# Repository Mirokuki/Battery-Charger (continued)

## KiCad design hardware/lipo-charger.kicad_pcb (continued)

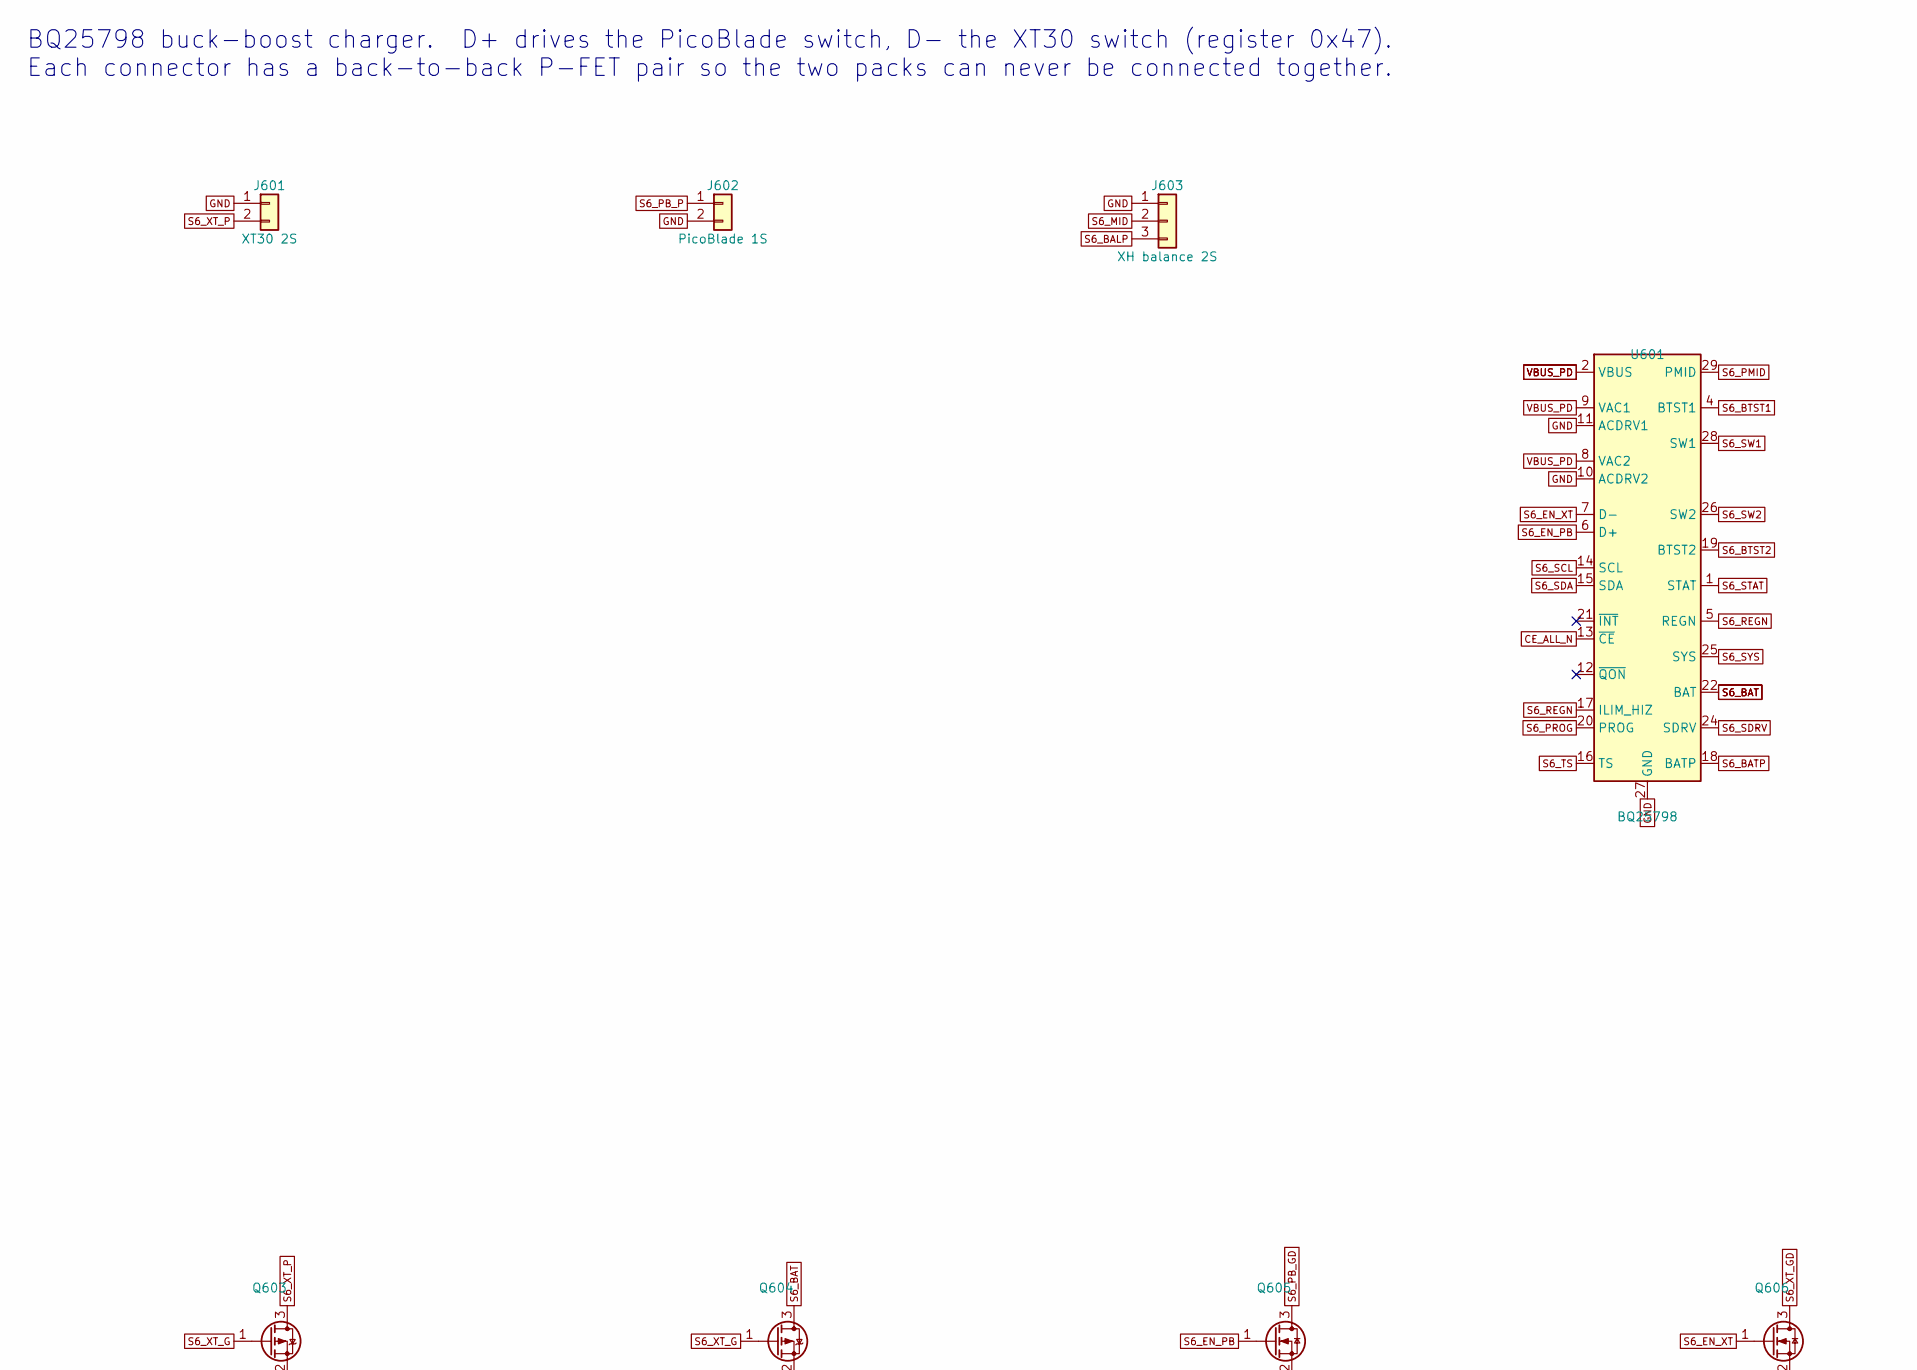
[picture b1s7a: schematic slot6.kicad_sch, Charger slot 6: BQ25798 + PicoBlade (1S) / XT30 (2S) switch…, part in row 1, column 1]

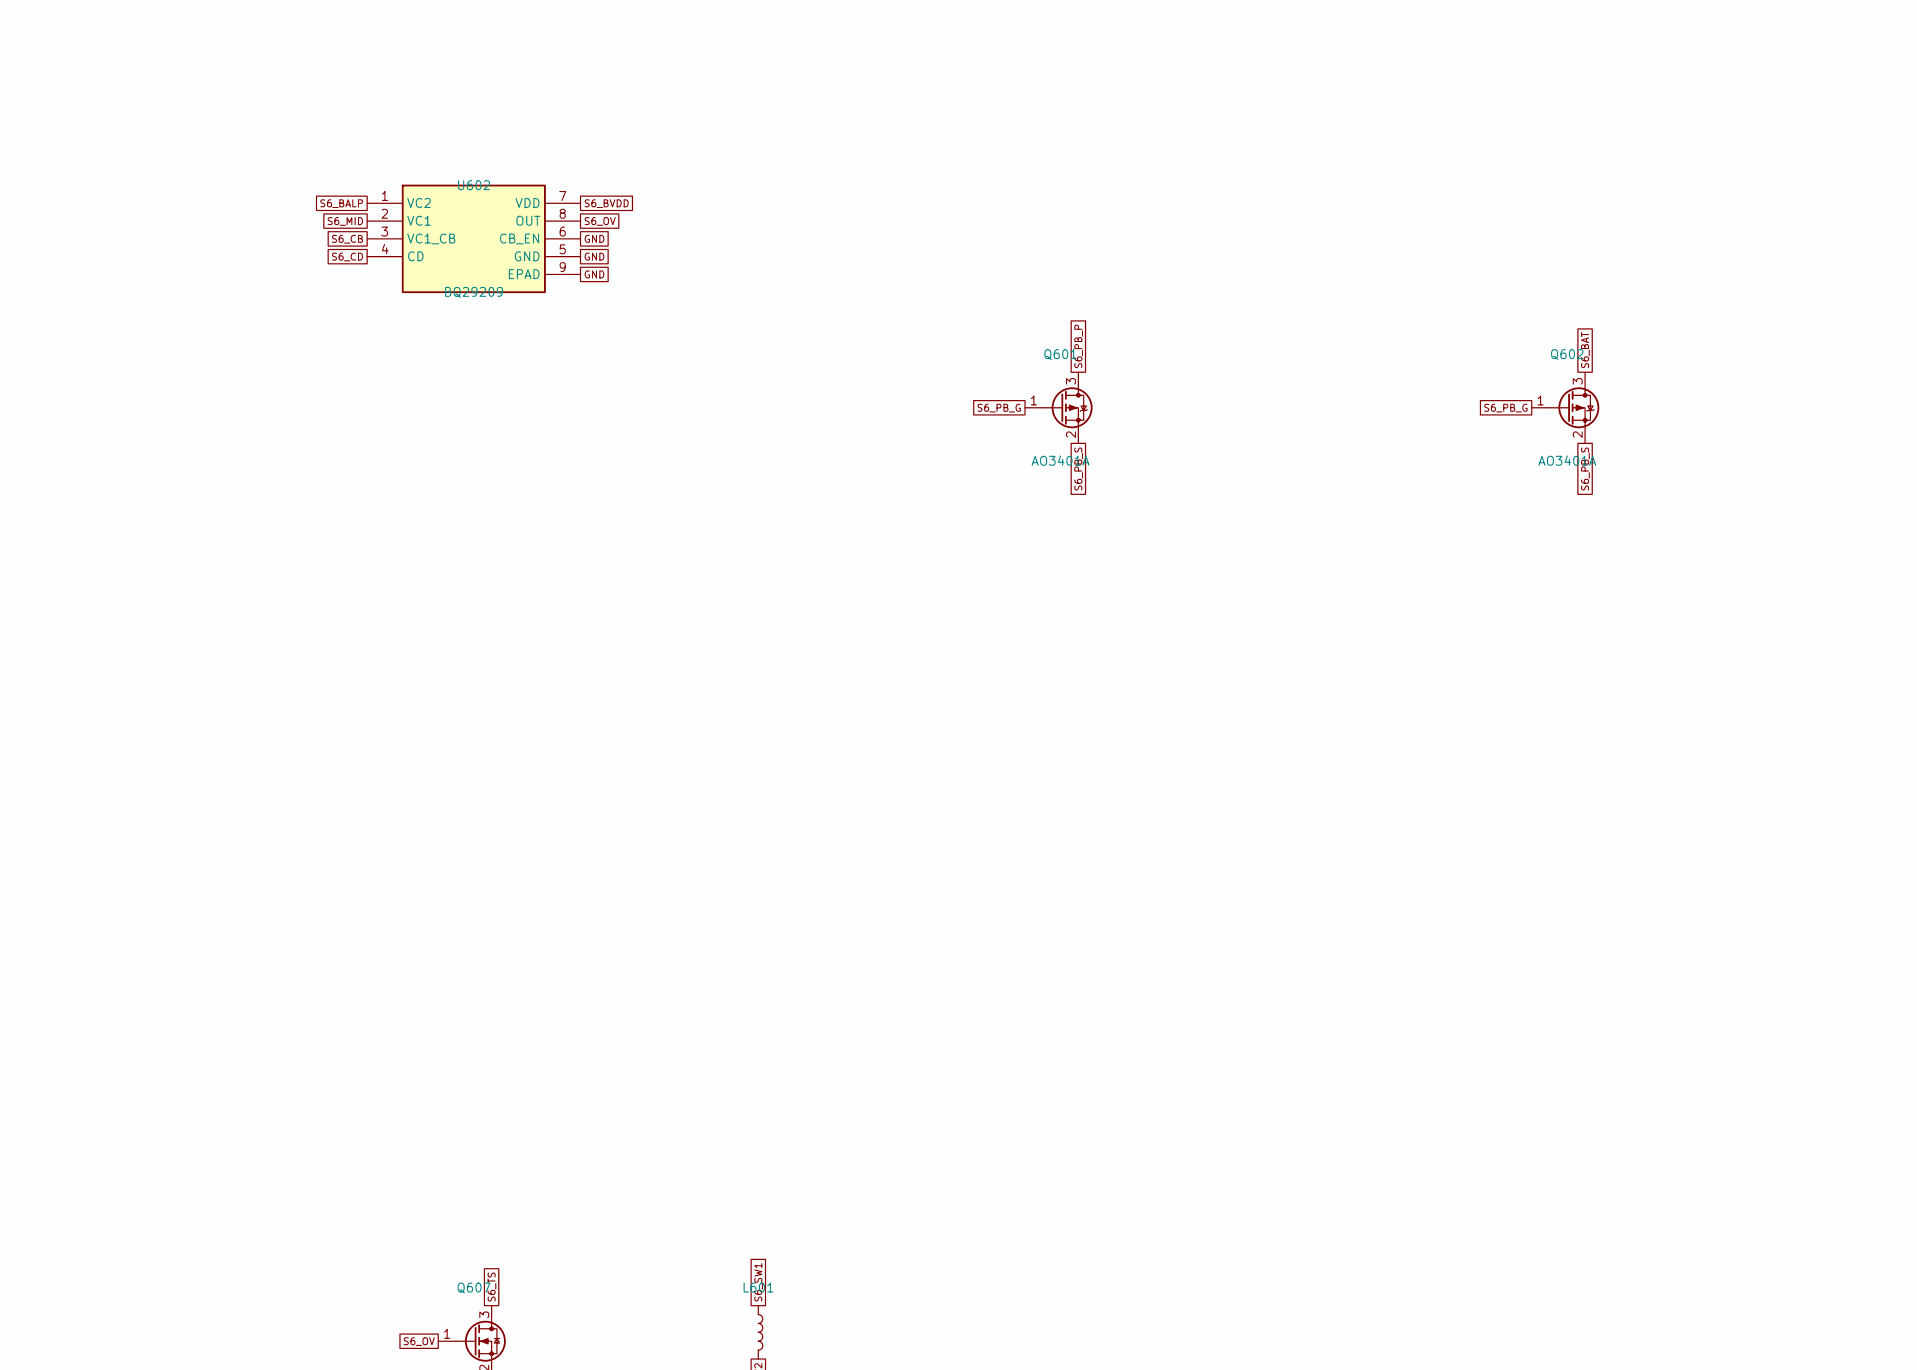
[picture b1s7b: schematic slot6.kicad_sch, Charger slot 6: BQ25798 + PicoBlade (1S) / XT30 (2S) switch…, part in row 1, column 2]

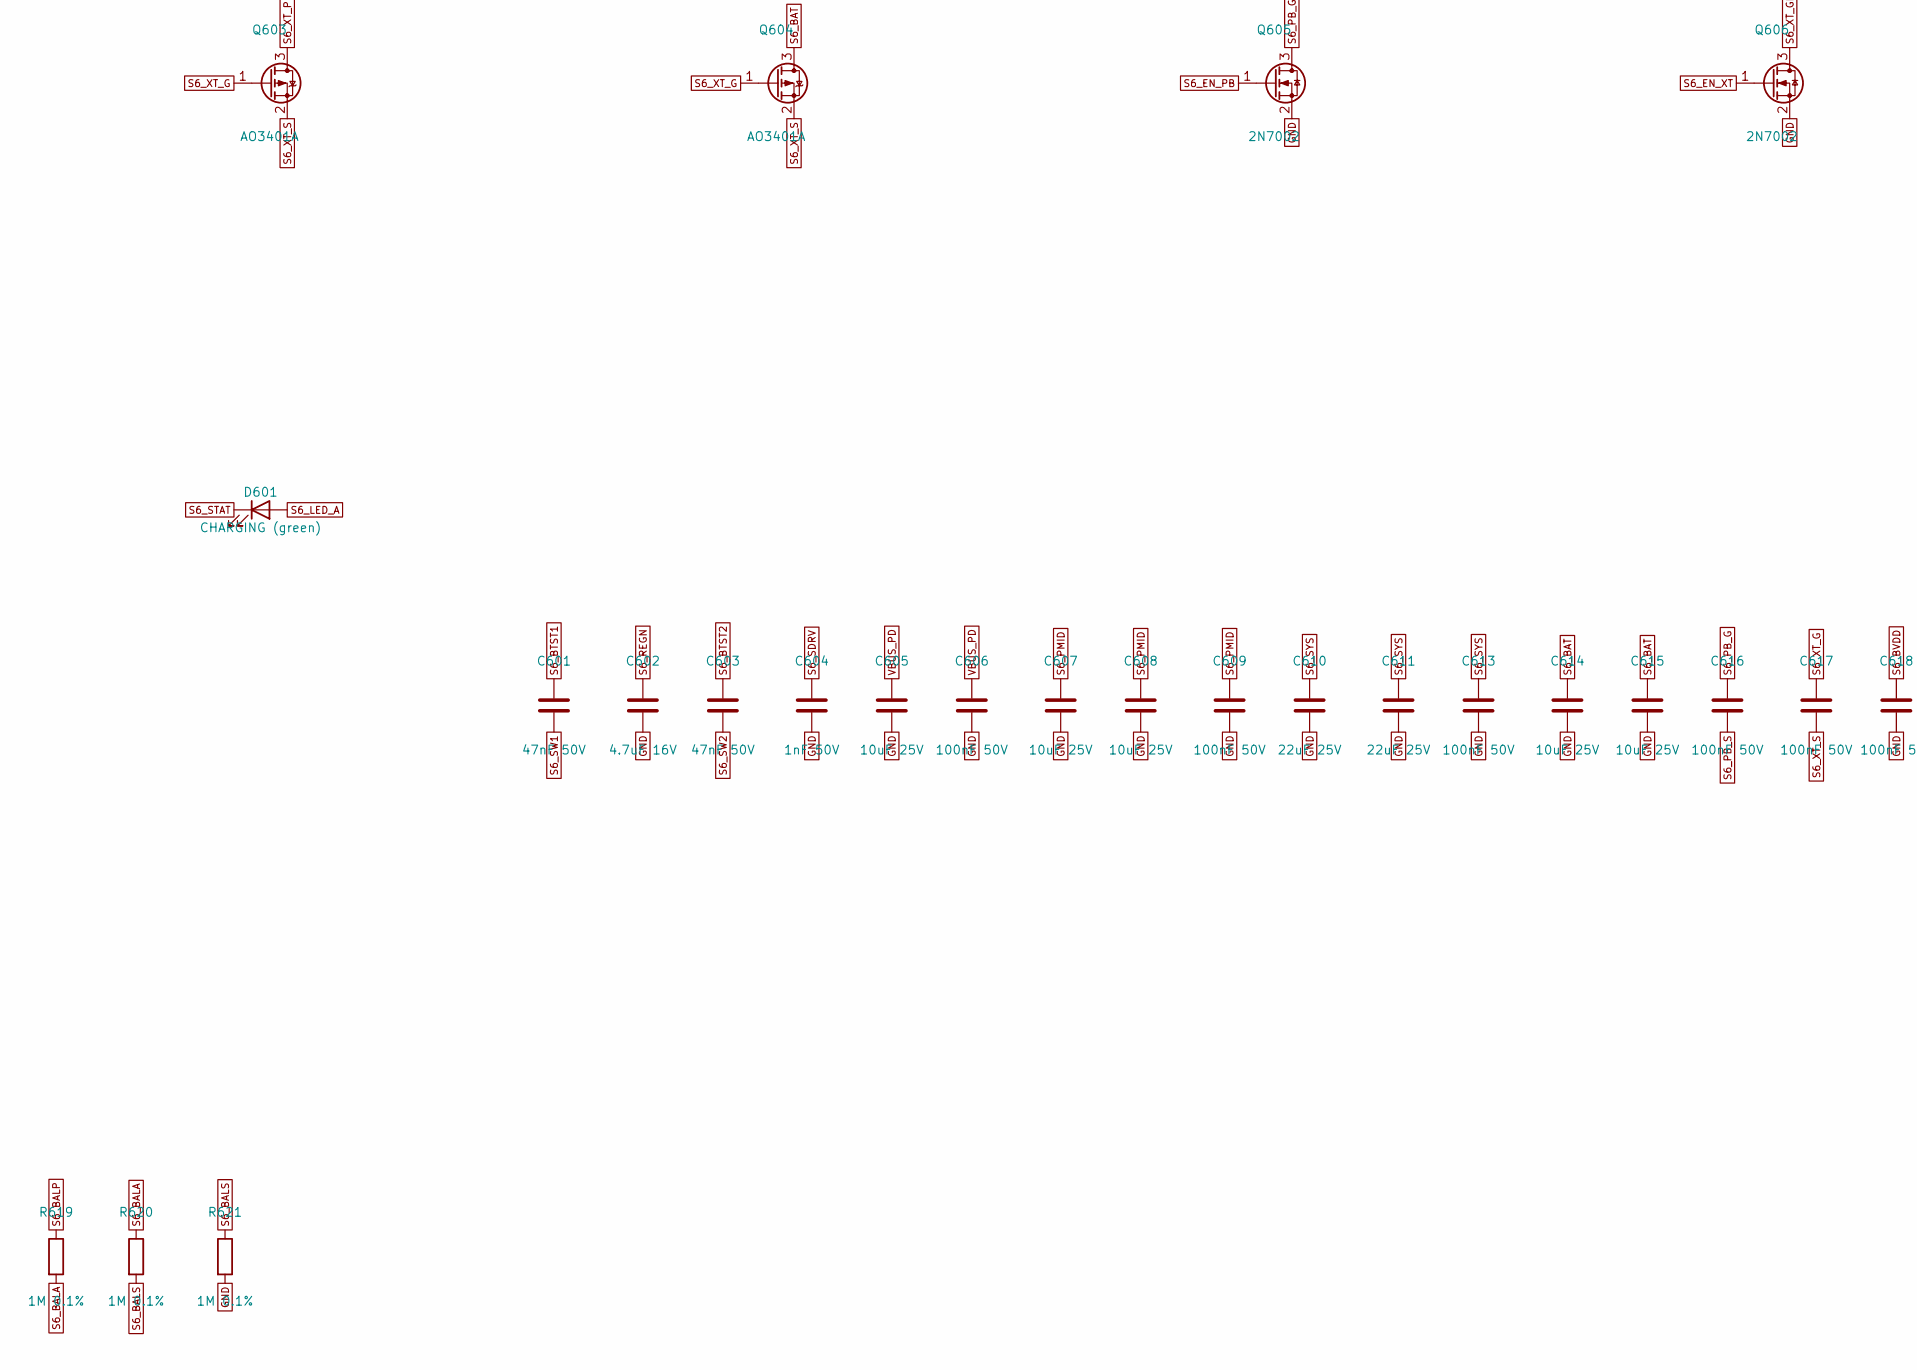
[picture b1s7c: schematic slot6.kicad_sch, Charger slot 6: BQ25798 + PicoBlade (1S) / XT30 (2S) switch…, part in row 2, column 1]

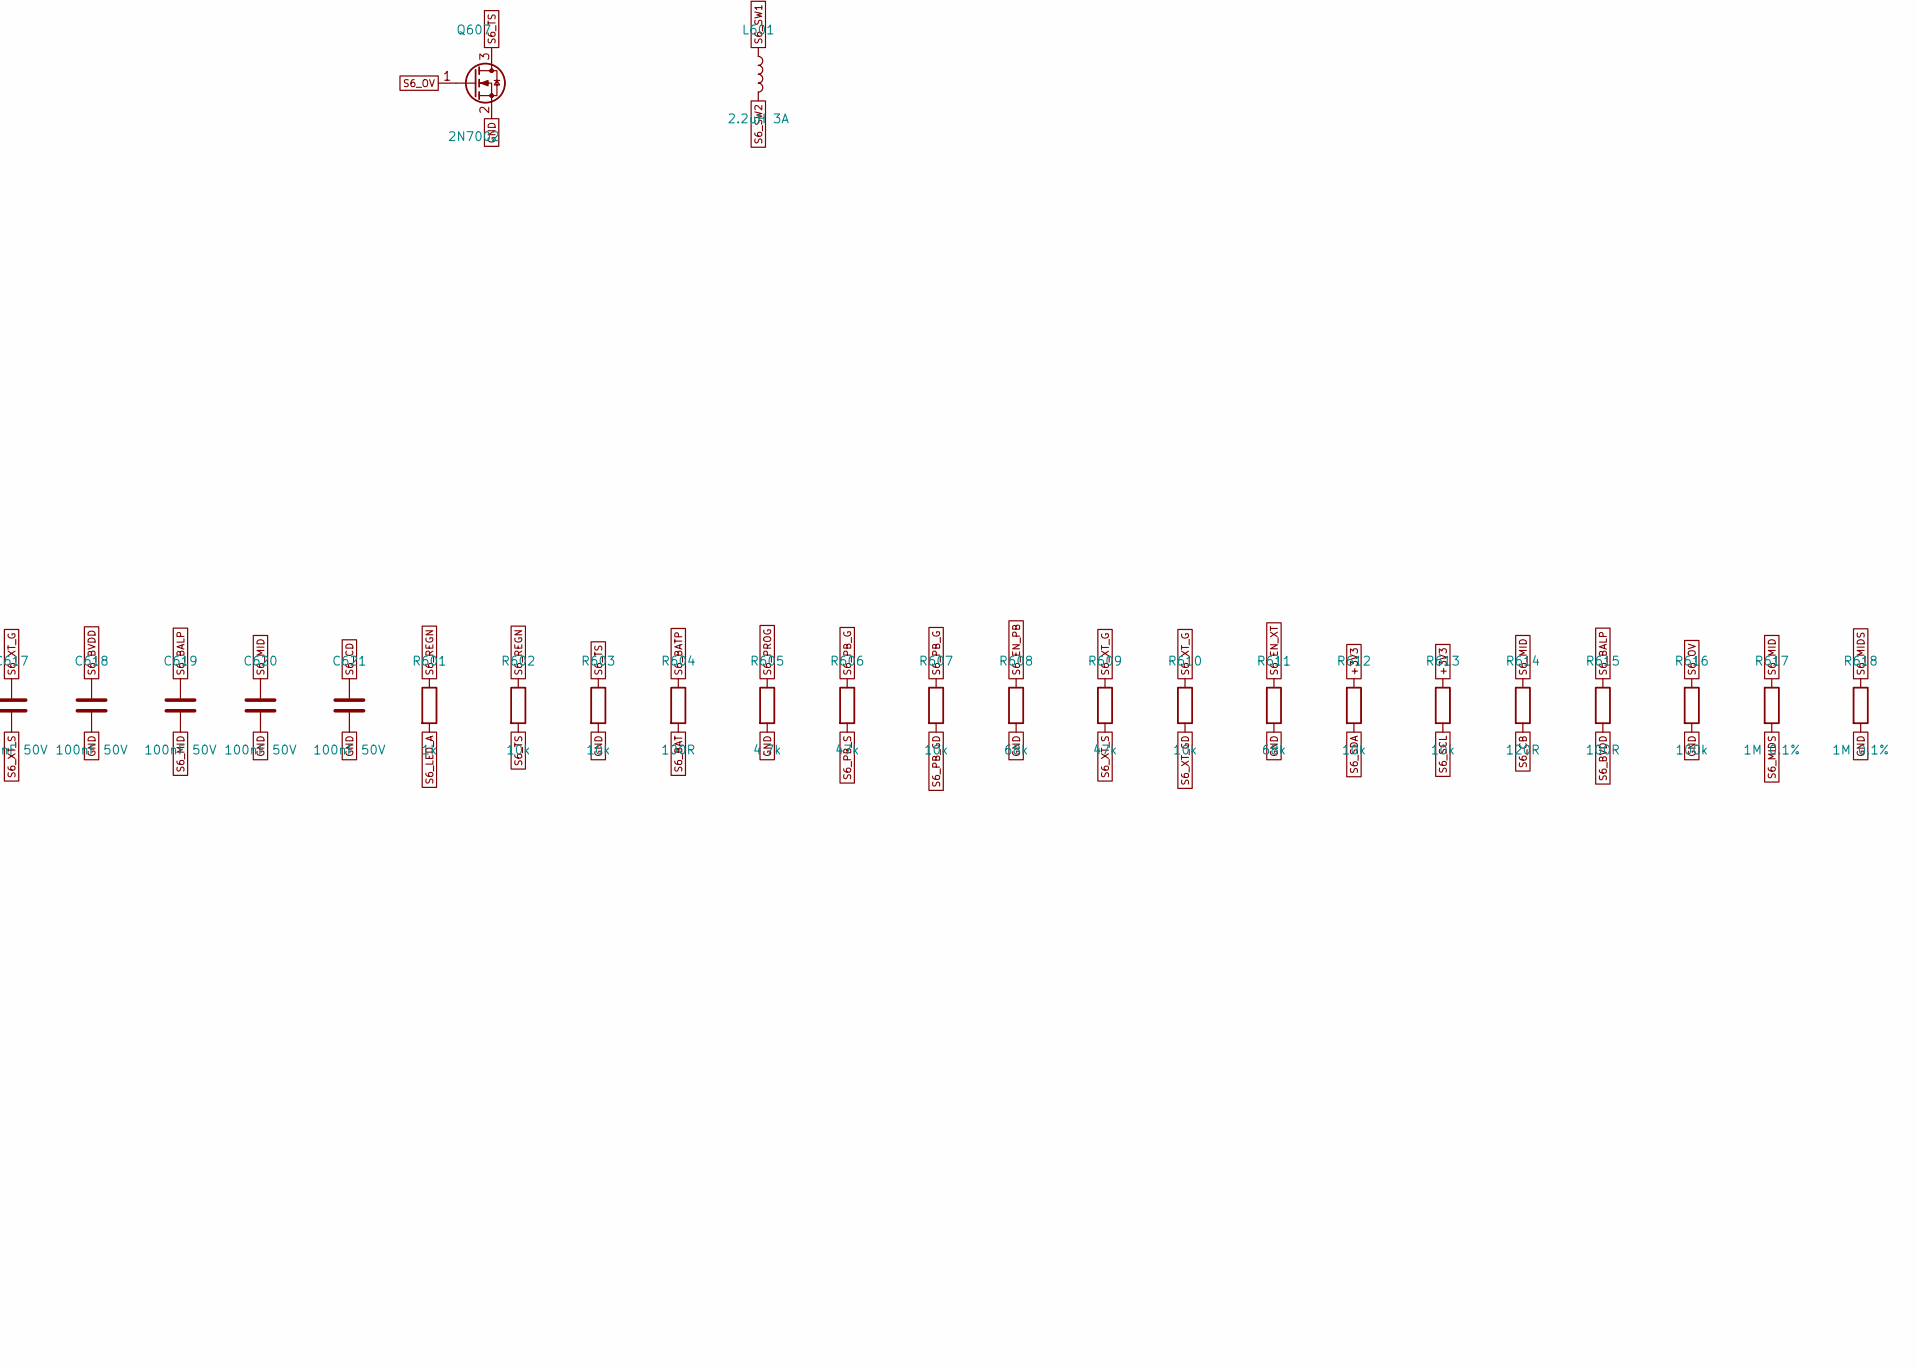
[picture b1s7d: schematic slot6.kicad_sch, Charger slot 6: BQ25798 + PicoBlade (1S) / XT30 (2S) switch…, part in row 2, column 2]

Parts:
C601, C603: 47nF 50V; C_0402_1005Metric; MPN CL05B473KB5NNNC
C602: 4.7uF 16V; C_0603_1608Metric; MPN CL10A475KO8NNNC; LCSC C19666
C604: 1nF 50V; C_0402_1005Metric; MPN CL05B102KB5NNNC; LCSC C1523
C605, C607, C608, C614, C615: 10uF 25V; C_0805_2012Metric; MPN CL21A106KAYNNNE; LCSC C15850
C606, C609, C613, C616, C617, C618, C619, C620, C621: 100nF 50V; C_0402_1005Metric; MPN CL05B104KB54PNC; LCSC C307331
C610, C611: 22uF 25V; C_0805_2012Metric; MPN CL21A226MAQNNNE; LCSC C45783
D601: CHARGING (green); LED_0603_1608Metric; MPN 19-217/GHC-YR1S2/3T; LCSC C72043
J601: XT30 2S; AMASS_XT30UPB-M_1x02_P5.0mm_Vertical; MPN XT30UPB-M; LCSC C99101
J602: PicoBlade 1S; Molex_PicoBlade_53047-0210_1x02_P1.25mm_Vertical; MPN 0530470210
J603: XH balance 2S; JST_XH_B3B-XH-A_1x03_P2.50mm_Vertical; MPN B3B-XH-A; LCSC C144394
L601: 2.2uH 3A; L_Changjiang_FNR4030S; MPN FNR4030S2R2MT
Q601, Q602, Q603, Q604: AO3401A; SOT-23; MPN AO3401A; LCSC C15127
Q605, Q606, Q607: 2N7002; SOT-23; MPN 2N7002; LCSC C8545
R601: 1k; R_0402_1005Metric; MPN 0402WGF1001TCE; LCSC C11702
R602, R603, R607, R610, R612, R613: 10k; R_0402_1005Metric; MPN 0402WGF1002TCE; LCSC C25744
R604, R615: 100R; R_0402_1005Metric; MPN 0402WGF1000TCE; LCSC C25076
R605: 4.7k; R_0402_1005Metric; MPN 0402WGF4701TCE; LCSC C25900
R606, R609: 47k; R_0402_1005Metric; MPN 0402WGF4702TCE; LCSC C25792
R608, R611: 68k; R_0402_1005Metric; MPN 0402WGF6802TCE; LCSC C36871
R614: 120R; R_0402_1005Metric; MPN 0402WGF1200TCE
R616: 100k; R_0402_1005Metric; MPN 0402WGF1003TCE; LCSC C25741
R617, R618, R619, R620, R621: 1M 0.1%; R_0402_1005Metric; MPN RT0402BRD071ML
U601: BQ25798; Texas_RQM0029A_VQFN-29_4x4mm_P0.4mm; MPN BQ25798RQMR; LCSC C2876768
U602: BQ29209; VSON-8-1EP_3x3mm_P0.65mm_EP1.65x2.4mm; MPN BQ29209DRBR

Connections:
+3V3: R612.1, R613.1; also elsewhere on the board
CE_ALL_N: U601.13 (~CE); also elsewhere on the board
GND: C602.2, C604.2, C605.2, C606.2, C607.2, C608.2, C609.2, C610.2, C611.2, C613.2, C614.2, C615.2, C618.2, C620.2, C621.2, J601.1, J602.2, J603.1, Q605.2 (S), Q606.2 (S), Q607.2 (S), R603.2, R605.2, R608.2, R611.2, R616.2, R618.2, R621.2, U601.10 (ACDRV2), U601.11 (ACDRV1), U601.27 (GND), U602.5 (GND), U602.6 (CB_EN), U602.9 (EPAD); also elsewhere on the board
S6_BALA: R619.2, R620.1
S6_BALP: C619.1, J603.3, R615.1, R619.1, U602.1 (VC2)
S6_BALS: R620.2, R621.1; also elsewhere on the board
S6_BAT: C614.1, C615.1, Q602.3 (D), Q604.3 (D), R604.2, U601.22 (BAT), U601.23 (BAT)
S6_BATP: R604.1, U601.18 (BATP)
S6_BTST1: C601.1, U601.4 (BTST1)
S6_BTST2: C603.1, U601.19 (BTST2)
S6_BVDD: C618.1, R615.2, U602.7 (VDD)
S6_CB: R614.2, U602.3 (VC1_CB)
S6_CD: C621.1, U602.4 (CD)
S6_EN_PB: Q605.1 (G), R608.1, U601.6 (D+)
S6_EN_XT: Q606.1 (G), R611.1, U601.7 (D-)
S6_LED_A: D601.2 (A), R601.2
S6_MID: C619.2, C620.1, J603.2, R614.1, R617.1, U602.2 (VC1)
S6_MIDS: R617.2, R618.1; also elsewhere on the board
S6_OV: Q607.1 (G), R616.1, U602.8 (OUT)
S6_PB_G: C616.1, Q601.1 (G), Q602.1 (G), R606.1, R607.1
S6_PB_GD: Q605.3 (D), R607.2
S6_PB_P: J602.1, Q601.3 (D)
S6_PB_S: C616.2, Q601.2 (S), Q602.2 (S), R606.2
S6_PMID: C607.1, C608.1, C609.1, U601.29 (PMID)
S6_PROG: R605.1, U601.20 (PROG)
S6_REGN: C602.1, R601.1, R602.1, U601.5 (REGN), U601.17 (ILIM_HIZ)
S6_SCL: R613.2, U601.14 (SCL); also elsewhere on the board
S6_SDA: R612.2, U601.15 (SDA); also elsewhere on the board
S6_SDRV: C604.1, U601.24 (SDRV)
S6_STAT: D601.1 (K), U601.1 (STAT)
S6_SW1: C601.2, L601.1, U601.28 (SW1)
S6_SW2: C603.2, L601.2, U601.26 (SW2)
S6_SYS: C610.1, C611.1, C613.1, U601.25 (SYS)
S6_TS: Q607.3 (D), R602.2, R603.1, U601.16 (TS)
S6_XT_G: C617.1, Q603.1 (G), Q604.1 (G), R609.1, R610.1
S6_XT_GD: Q606.3 (D), R610.2
S6_XT_P: J601.2, Q603.3 (D)
S6_XT_S: C617.2, Q603.2 (S), Q604.2 (S), R609.2
VBUS_PD: C605.1, C606.1, U601.2 (VBUS), U601.3 (VBUS), U601.8 (VAC2), U601.9 (VAC1); also elsewhere on the board

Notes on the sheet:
BQ25798 buck-boost charger. D+ drives the PicoBlade switch, D- the XT30 switch (register 0x47). Each connector has a back-to-back P-FET pair so the two packs can never be connected together.

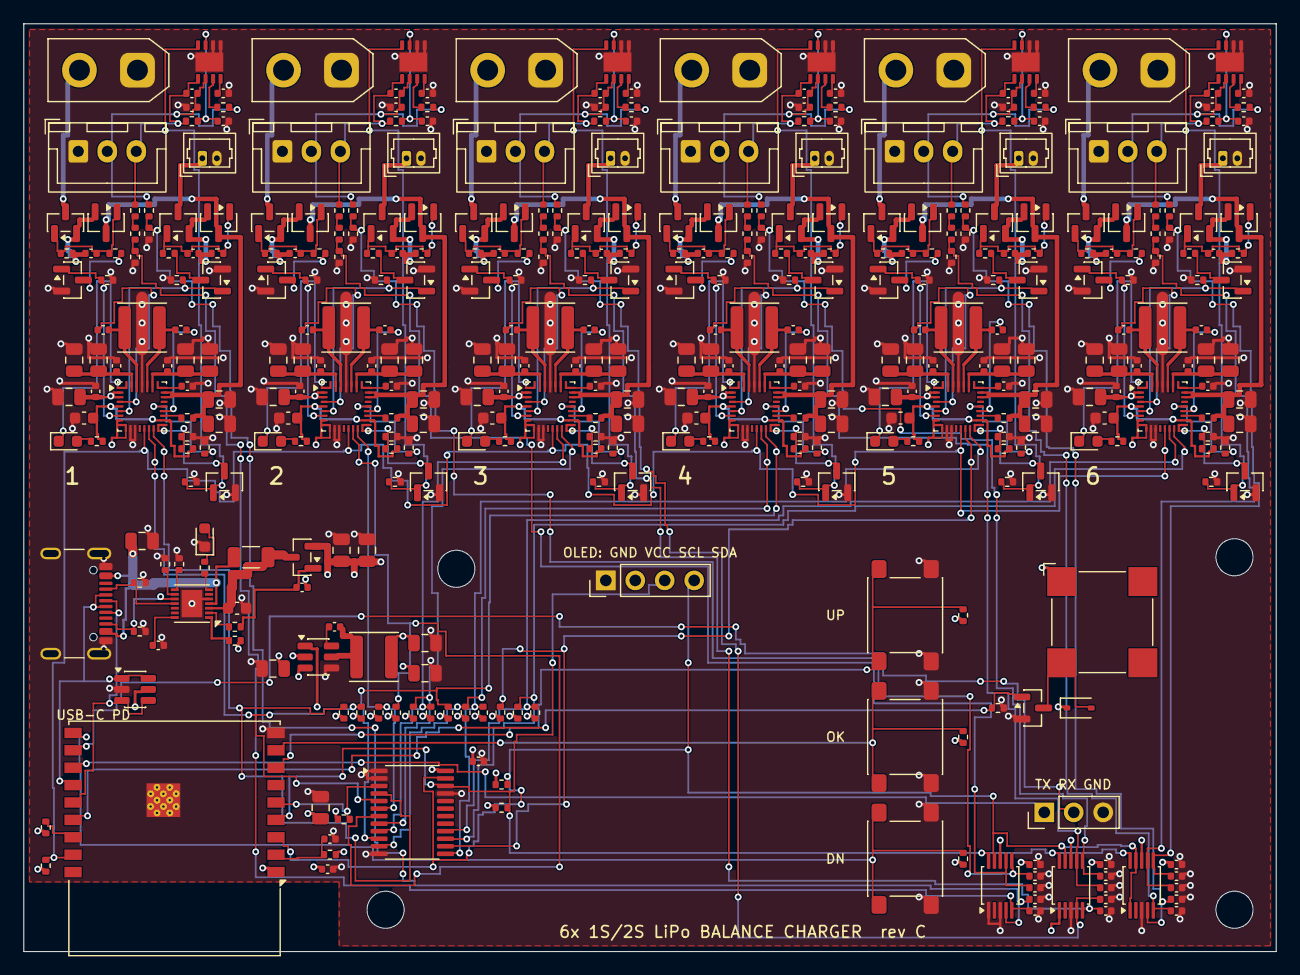
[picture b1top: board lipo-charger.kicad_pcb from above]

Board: 4 copper layers, 108.0 x 80.0 mm, 401 parts (0 on the bottom side), 242 nets.

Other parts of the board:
H1, H2, H3, H4: MountingHole_3.2mm_M3

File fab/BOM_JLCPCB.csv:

Comment,Designator,Footprint,LCSC Part #,MPN,Qty,Assembly
CMT-8504-100-SMT,BZ1,MagneticBuzzer_CUI_CMT-8504-100-SMT,,CMT-8504-100-SMT-TR,1,SMT
100nF 50V,"C1,C8,C12,C14,C20,C21,C22,C23,C24,C25,C26,C27,C28,C29,C30,C31,C32,C33,C34,C106,C109,C113,C116,C117,C118,C119,C120,C121,C206,C209,C213,C216,C217,C218,C219,C220,C221,C306,C309,C313,C316,C317,C318,C319,C320,C321,C406,C409,C413,C416,C417,C418,C419,C420,C421,C506,C509,C513,C516,C517,C518,C519,C520,C521,C606,C609,C613,C616,C617,C618,C619,C620,C621",C_0402_1005Metric,C307331,CL05B104KB54PNC,73,SMT
1uF 50V,C2,C_0603_1608Metric,C15849,CL10A105KB8NNNC,1,SMT
1uF 16V,"C3,C13",C_0402_1005Metric,C52923,CL05A105KA5NQNC,2,SMT
10uF 25V,"C4,C5,C6,C7,C11,C105,C107,C108,C114,C115,C205,C207,C208,C214,C215,C305,C307,C308,C314,C315,C405,C407,C408,C414,C415,C505,C507,C508,C514,C515,C605,C607,C608,C614,C615",C_0805_2012Metric,C15850,CL21A106KAYNNNE,35,SMT
22uF 25V,"C9,C10,C110,C111,C210,C211,C310,C311,C410,C411,C510,C511,C610,C611",C_0805_2012Metric,C45783,CL21A226MAQNNNE,14,SMT
47nF 50V,"C101,C103,C201,C203,C301,C303,C401,C403,C501,C503,C601,C603",C_0402_1005Metric,,CL05B473KB5NNNC,12,SMT
4.7uF 16V,"C102,C202,C302,C402,C502,C602",C_0603_1608Metric,C19666,CL10A475KO8NNNC,6,SMT
1nF 50V,"C104,C204,C304,C404,C504,C604",C_0402_1005Metric,C1523,CL05B102KB5NNNC,6,SMT
PD OK (blue),D1,LED_0603_1608Metric,C72041,19-217/BHC-ZL1M2RY/3T,1,SMT
1N4148WS,D2,D_SOD-323,C2128,1N4148WS,1,SMT
CHARGING (green),"D101,D201,D301,D401,D501,D601",LED_0603_1608Metric,C72043,19-217/GHC-YR1S2/3T,6,SMT
USB4105-GF-A,J1,USB_C_Receptacle_GCT_USB4105-xx-A_16P_TopMnt_Horizontal,C3020560,USB4105-GF-A,1,SMT
OLED 0.96in SSD1306 (GND VCC SCL SDA),J2,PinHeader_1x04_P2.54mm_Vertical,,,1,hand-solder (through-hole)
XT30 2S,"J101,J201,J301,J401,J501,J601",AMASS_XT30UPB-M_1x02_P5.0mm_Vertical,C99101,XT30UPB-M,6,hand-solder (through-hole)
PicoBlade 1S,"J102,J202,J302,J402,J502,J602",Molex_PicoBlade_53047-0210_1x02_P1.25mm_Vertical,,0530470210,6,hand-solder (through-hole)
XH balance 2S,"J103,J203,J303,J403,J503,J603",JST_XH_B3B-XH-A_1x03_P2.50mm_Vertical,C144394,B3B-XH-A,6,hand-solder (through-hole)
4.7uH 2A,L1,L_Changjiang_FNR4030S,,FNR4030S4R7MT,1,SMT
2.2uH 3A,"L101,L201,L301,L401,L501,L601",L_Changjiang_FNR4030S,,FNR4030S2R2MT,6,SMT
AO3400A,Q1,SOT-23,C20917,AO3400A,1,SMT
2N7002,"Q2,Q105,Q106,Q107,Q205,Q206,Q207,Q305,Q306,Q307,Q405,Q406,Q407,Q505,Q506,Q507,Q605,Q606,Q607",SOT-23,C8545,2N7002,19,SMT
AO3401A,"Q101,Q102,Q103,Q104,Q201,Q202,Q203,Q204,Q301,Q302,Q303,Q304,Q401,Q402,Q403,Q404,Q501,Q502,Q503,Q504,Q601,Q602,Q603,Q604",SOT-23,C15127,AO3401A,24,SMT
5.1k,"R1,R2",R_0402_1005Metric,C25905,0402WGF5101TCE,2,SMT
5mR 1%,R3,R_1206_3216Metric,,PE1206FKF470R005Z,1,SMT
6.2k,R4,R_0402_1005Metric,,0402WGF6201TCE,1,SMT
200R,R5,R_0402_1005Metric,C25087,0402WGF2000TCE,1,SMT
82k,R6,R_0402_1005Metric,C25958,0402WGF8202TCE,1,SMT
100k,"R7,R17,R116,R216,R316,R416,R516,R616",R_0402_1005Metric,C25741,0402WGF1003TCE,8,SMT
2.2k,R8,R_0402_1005Metric,C25879,0402WGF2201TCE,1,SMT
10k,"R9,R10,R11,R14,R15,R16,R18,R102,R103,R107,R110,R112,R113,R202,R203,R207,R210,R212,R213,R302,R303,R307,R310,R312,R313,R402,R403,R407,R410,R412,R413,R502,R503,R507,R510,R512,R513,R602,R603,R607,R610,R612,R613",R_0402_1005Metric,C25744,0402WGF1002TCE,43,SMT
4.7k,"R12,R13,R105,R205,R305,R405,R505,R605",R_0402_1005Metric,C25900,0402WGF4701TCE,8,SMT
1k,"R101,R201,R301,R401,R501,R601",R_0402_1005Metric,C11702,0402WGF1001TCE,6,SMT
100R,"R104,R115,R204,R215,R304,R315,R404,R415,R504,R515,R604,R615",R_0402_1005Metric,C25076,0402WGF1000TCE,12,SMT
47k,"R106,R109,R206,R209,R306,R309,R406,R409,R506,R509,R606,R609",R_0402_1005Metric,C25792,0402WGF4702TCE,12,SMT
68k,"R108,R111,R208,R211,R308,R311,R408,R411,R508,R511,R608,R611",R_0402_1005Metric,C36871,0402WGF6802TCE,12,SMT
120R,"R114,R214,R314,R414,R514,R614",R_0402_1005Metric,,0402WGF1200TCE,6,SMT
1M 0.1%,"R117,R118,R119,R120,R121,R217,R218,R219,R220,R221,R317,R318,R319,R320,R321,R417,R418,R419,R420,R421,R517,R518,R519,R520,R521,R617,R618,R619,R620,R621",R_0402_1005Metric,,RT0402BRD071ML,30,SMT
BTN_UP,SW1,SW_SPST_PTS645Sx43SMTR92,,PTS645SM95SMTR92 LFS,1,SMT
BTN_OK,SW2,SW_SPST_PTS645Sx43SMTR92,,PTS645SM95SMTR92 LFS,1,SMT
BTN_DN,SW3,SW_SPST_PTS645Sx43SMTR92,,PTS645SM95SMTR92 LFS,1,SMT
AP33771C,U1,DFN-14-1EP_3x3mm_P0.4mm_EP1.78x2.35mm,,AP33771CFBZ-13-FA02,1,SMT
AP63203WU,U2,TSOT-23-6,C780769,AP63203WU-7,1,SMT
ESP32-C3-WROOM-02-N4,U3,ESP32-C3-WROOM-02,C2934560,ESP32-C3-WROOM-02-N4,1,SMT
USBLC6-2SC6,U4,SOT-23-6,C7519,USBLC6-2SC6,1,SMT
TCA9548APWR,U5,TSSOP-24_4.4x7.8mm_P0.65mm,C130026,TCA9548APWR,1,SMT
ADS1115,"U6,U7,U8",TSSOP-10_3x3mm_P0.5mm,C37593,ADS1115IDGSR,3,SMT
BQ25798,"U101,U201,U301,U401,U501,U601",Texas_RQM0029A_VQFN-29_4x4mm_P0.4mm,C2876768,BQ25798RQMR,6,SMT
BQ29209,"U102,U202,U302,U402,U502,U602",VSON-8-1EP_3x3mm_P0.65mm_EP1.65x2.4mm,,BQ29209DRBR,6,SMT
